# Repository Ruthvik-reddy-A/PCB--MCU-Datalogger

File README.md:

# 🧾 MCU Data Logger – PCB Design

This repository contains the complete PCB design files and documentation for a microcontroller-based data logger with 512KB external EEPROM. The system is designed to log sensor data and store it in non-volatile memory, making it ideal for long-term, standalone data acquisition applications.

---

🔧 Designed using: KiCad 

📐 PCB Type: 2-layer, through-hole/SMD hybrid

---

## 🔋 Key Features
* Microcontroller-based core (ATmega328P / STM32 / ESP32)
* 512KB I²C EEPROM (e.g., 24LC512) for data storage
* Optional RTC (DS3231) for timestamped logging
* UART/USB interface for data extraction
* Breadboard-compatible or standalone PCB footprint
* Power input: USB / 5V header / Li-Ion with LDO
---

## 🔧 Hardware Block Diagram

## 🖼️ PCB Preview
Top View of the PCB:

Back View (if applicable):

---

## 📐 Pinouts & Interfaces

| Interface | Purpose               | Pin(s)            |
| --------- | --------------------- | ----------------- |
| I²C       | EEPROM, RTC           | SDA, SCL          |
| UART      | Serial communication  | TX, RX            |
| Power     | +5V / GND / Battery   | VIN, GND          |
| Sensor    | Analog/Digital inputs | A0, A1, D2, D3... |

---

## 📥 Data Logging Behavior
* Data sampled every X seconds
* Stored in EEPROM in binary or CSV-friendly format
* Memory managed using circular buffer logic
* Data dump via UART/USB when connected to host

---

## 🛠️ Fabrication & Assembly
* Use the included Gerber files (/gerbers) for fabrication
* Reference BOM (/bom.csv) for components
* Optionally reflow or hand-solder depending on design

---

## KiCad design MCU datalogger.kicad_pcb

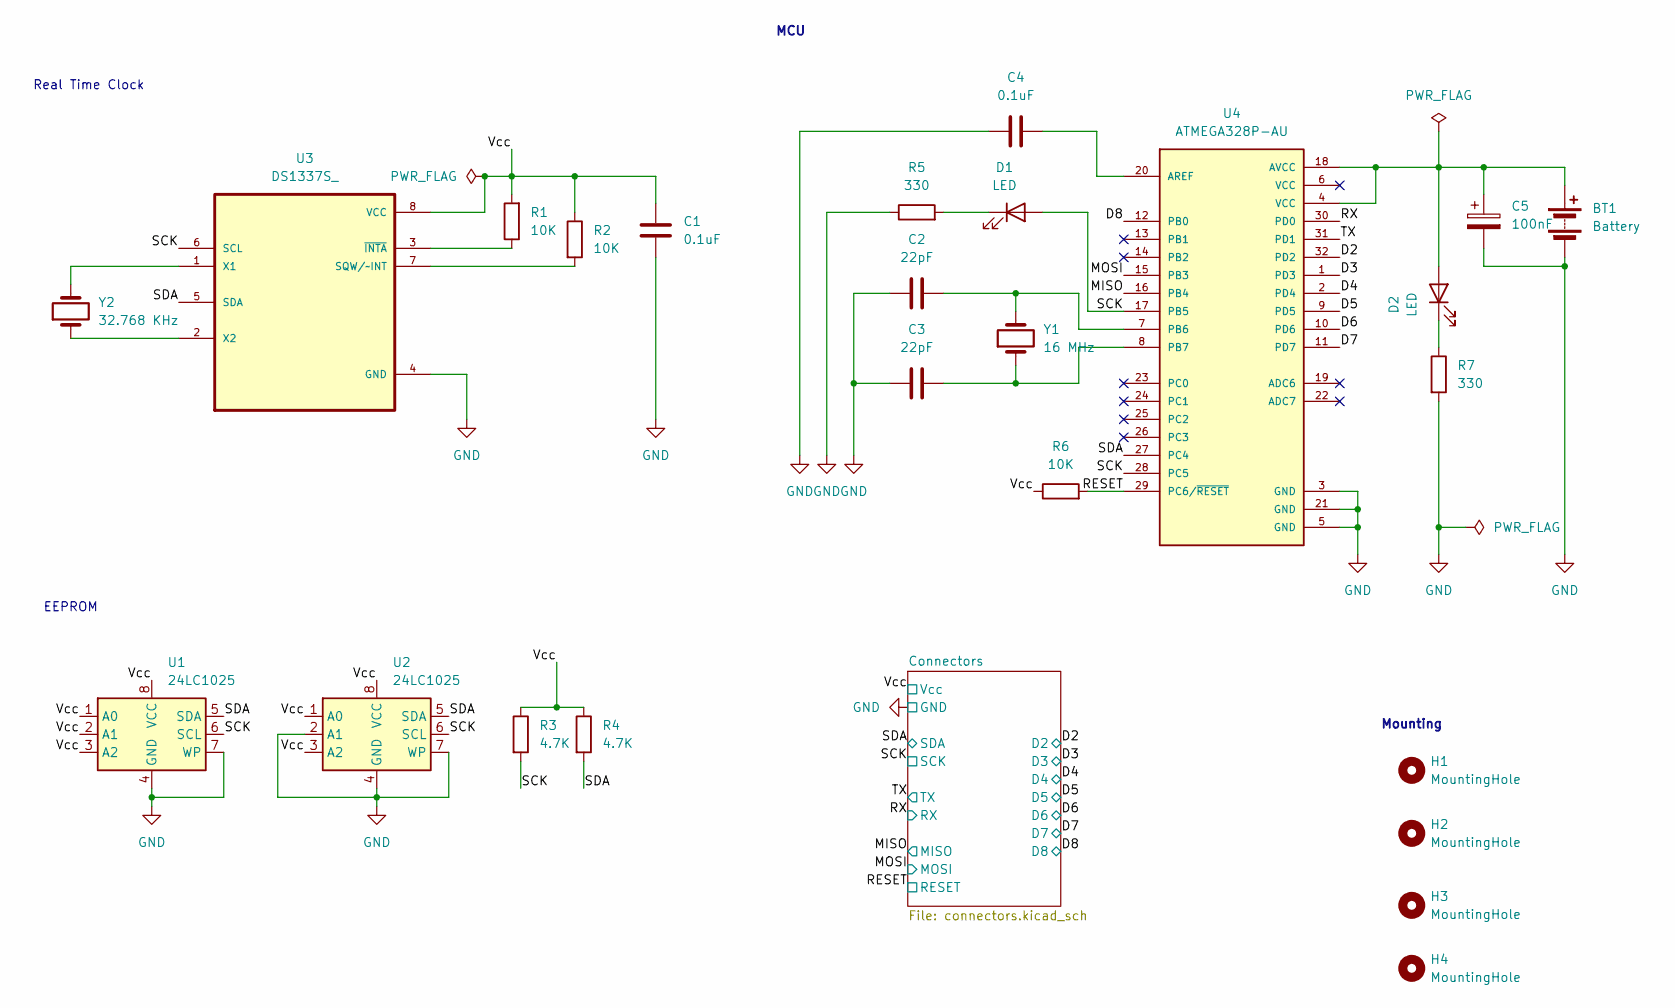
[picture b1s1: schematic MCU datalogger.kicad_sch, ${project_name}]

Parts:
BT1: Battery; PinHeader_1x02_P2.54mm_Vertical
C1, C4: 0.1uF; C_0805_2012Metric
C2, C3: 22pF; C_0805_2012Metric
C5: 100nF; C_0805_2012Metric
D1, D2: LED; LED_0805_2012Metric
H1, H2, H3, H4: MountingHole; MountingHole_2.1mm
R1, R2, R6: 10K; R_0805_2012Metric
R3, R4: 4.7K; R_0805_2012Metric
R5, R7: 330; R_0805_2012Metric
U1, U2: 24LC1025; SOIC-8_5.3x5.3mm_P1.27mm
U3: DS1337S_; SOIC127P600X175-8N
U4: ATMEGA328P-AU; QFP80P900X900X120-32N; PARTREV 8271A
Y1: 16 MHz; Crystal_SMD_5032-2Pin_5.0x3.2mm_HandSoldering
Y2: 32.768 KHz; Crystal_SMD_5032-2Pin_5.0x3.2mm_HandSoldering

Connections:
/D2: U4.32 (PD2); also elsewhere on the board
/D3: U4.1 (PD3); also elsewhere on the board
/D4: U4.2 (PD4); also elsewhere on the board
/D5: U4.9 (PD5); also elsewhere on the board
/D6: U4.10 (PD6); also elsewhere on the board
/D7: U4.11 (PD7); also elsewhere on the board
/D8: U4.12 (PB0); also elsewhere on the board
/MISO: U4.16 (PB4); also elsewhere on the board
/MOSI: U4.15 (PB3); also elsewhere on the board
/RESET: R6.2, U4.29 (PC6/~RESET); also elsewhere on the board
/RX: U4.30 (PD0); also elsewhere on the board
/SCK: D1.2 (A), R3.2, U1.6 (SCL), U2.6 (SCL), U3.6 (SCL), U4.17 (PB5), U4.28 (PC5); also elsewhere on the board
/SDA: R4.2, U1.5 (SDA), U2.5 (SDA), U3.5 (SDA), U4.27 (PC4); also elsewhere on the board
/TX: U4.31 (PD1); also elsewhere on the board
GND: BT1.2 (-), C1.2, C2.1, C3.1, C4.1, C5.2, R5.1, R7.2, U1.4 (GND), U1.7 (WP), U2.2 (A1), U2.4 (GND), U2.7 (WP), U3.4 (GND), U4.3 (GND), U4.5 (GND), U4.21 (GND); also elsewhere on the board
unnamed: D1.1 (K), R5.2
unnamed: D2.1 (K), R7.1
unnamed: R2.2, U3.7 (SQW/~INT)
unnamed: U3.1 (X1), Y2.2
unnamed: U3.2 (X2), Y2.1
unnamed: R1.1, U3.3 (~INTA)
unnamed: C4.2, U4.20 (AREF)
unnamed: C2.2, U4.7 (PB6), Y1.2
unnamed: C3.2, U4.8 (PB7), Y1.1

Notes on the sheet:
Real Time Clock
Mounting
MCU
EEPROM

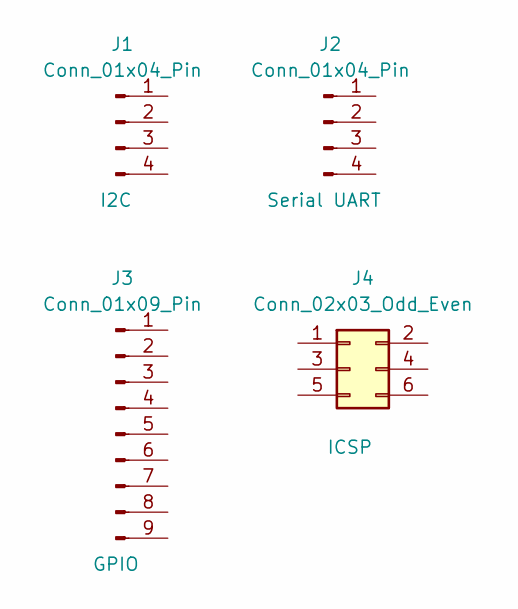
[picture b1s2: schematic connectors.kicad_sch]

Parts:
J1, J2: Conn_01x04_Pin; PinHeader_1x04_P2.54mm_Vertical
J3: Conn_01x09_Pin; PinHeader_1x09_P2.54mm_Vertical
J4: Conn_02x03_Odd_Even; PinHeader_2x03_P2.54mm_Vertical

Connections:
/D2: J3.1; also elsewhere on the board
/D3: J3.2; also elsewhere on the board
/D4: J3.3; also elsewhere on the board
/D5: J3.4; also elsewhere on the board
/D6: J3.5; also elsewhere on the board
/D7: J3.6; also elsewhere on the board
/D8: J3.7; also elsewhere on the board
/MISO: J4.1; also elsewhere on the board
/MOSI: J4.4; also elsewhere on the board
/RESET: J4.5; also elsewhere on the board
/RX: J2.3; also elsewhere on the board
/SCK: J1.4, J4.3; also elsewhere on the board
/SDA: J1.3; also elsewhere on the board
/TX: J2.4; also elsewhere on the board
GND: J1.1, J2.1, J3.8, J4.6; also elsewhere on the board

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
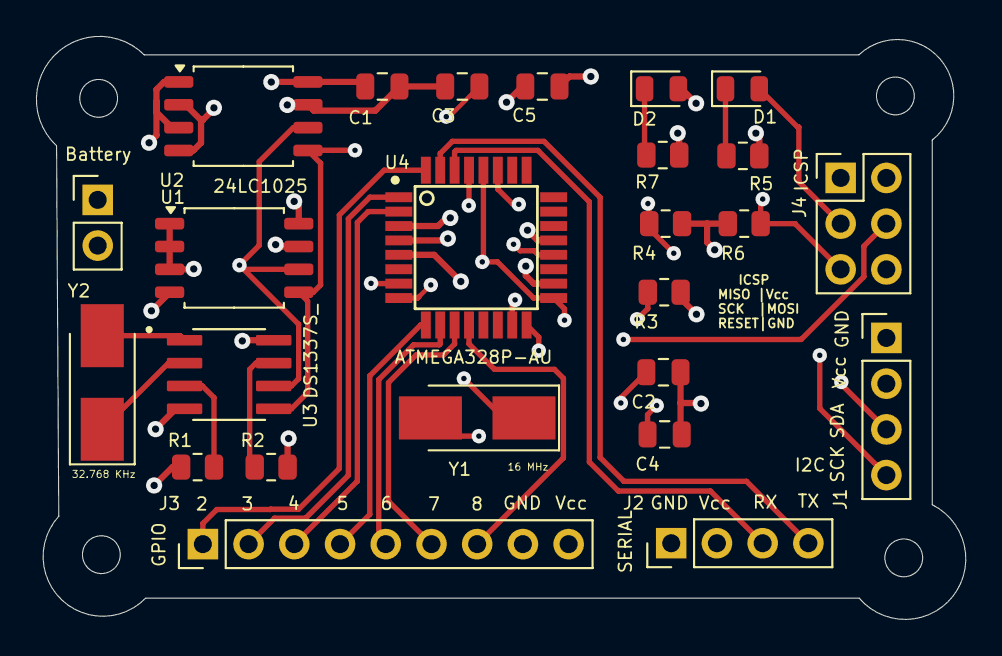
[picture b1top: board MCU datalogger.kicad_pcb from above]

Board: 4 copper layers, 51.6 x 32.4 mm, 29 parts (0 on the bottom side), 25 nets.

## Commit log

2025-05-23 First commit of new proj
2025-05-23 Setup of EEschema for new project
2025-05-23 Symbols added to schematic
2025-05-26 main
2025-05-26 updates to files
2025-05-26 changed location of symbols
2025-05-26 completed symbols footprints association
2025-05-27 Completed wiring of main sheet
2025-05-27 changes in both sheets
2025-05-27 Completed Schematic dsgn
2025-05-27 Modified gitignore
2025-05-27 Untracked library, cache, and backup files
2025-05-27 changes to git
2025-05-27 Completed placement of footprints
2025-05-28 Routing and GND Vcc complete
2025-05-30 completed routing
2025-05-30 Completed Design of 2-layer
2025-05-30 Gerbers added
2025-05-30 completed 2 layer project
2025-06-03 Added gerber directeries to gitignore
2025-06-05 completed 4layer pcb routing
2025-06-10 Guide for Project
